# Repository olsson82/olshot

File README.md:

# OlShot
This is an Arduino based Shooting game system. Free to use, you need to make the components your self.

It's wireless and uses nrf24l01 modules to communicate to the targets and the main system.

## How mutch does it cost to buid ?
Well it will cost you some money, for the components, and maufactoring the pcb, **BUT** to have your custom build game is priceless.

## Many Targets
If you are going to use many targets, you need to redesign main unit pcb to work with **ATmega2560** chip (same as in Arduino Mega)
The code here is by default set for 5 targets, but you can adjust it. Test the code in Arduino software when you change to see if your amount of targets
is accepted.

# Read more
* [Wiki](https://github.com/olsson82/olshot/wiki)
* [Targets](page/targets.md)
* [Main Unit](page/mainunit.md)

## Updates
**2023-09-01: Did a redesign on the Nextion Screen. Files uploaded**

**2023-08-31: The clock function is now added to the code, and some adjustments done in the code**

**2023-08-30: The first BETA version of main unit is released.**

**2023-08-04: Working on the code for main unit and design for the touchscreen.**

### Main Unit
**2023-08-01: Kicad files now uploaded**

**2023-07-31: The main unit has been tested and everything seems to be working. The kicad files will soon be uploaded.**

<figure>
    
    <figcaption>Front side of the PCB.</figcaption>
</figure>

### Target PCB
**2023-02-05: The Target PCB Is now avalible for kicad and arduino code.**

Did a redesign of the target sensor, everything is now on the top side. Added jst connections instead of soldering.
<figure>
    
    <figcaption>Front side of the PCB.</figcaption>
</figure>

## Discuss
Feel free to take part in this project. Go to [Discussion](https://github.com/olsson82/olshot/discussions) to ask questions or discuss about the project.

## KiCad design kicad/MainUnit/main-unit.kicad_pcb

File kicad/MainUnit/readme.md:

# Main Unit
This is the main unit. You also need target sensors for it to work.
Please read the WIKI about this main unit before manufactor so you know everything.

Good luck!

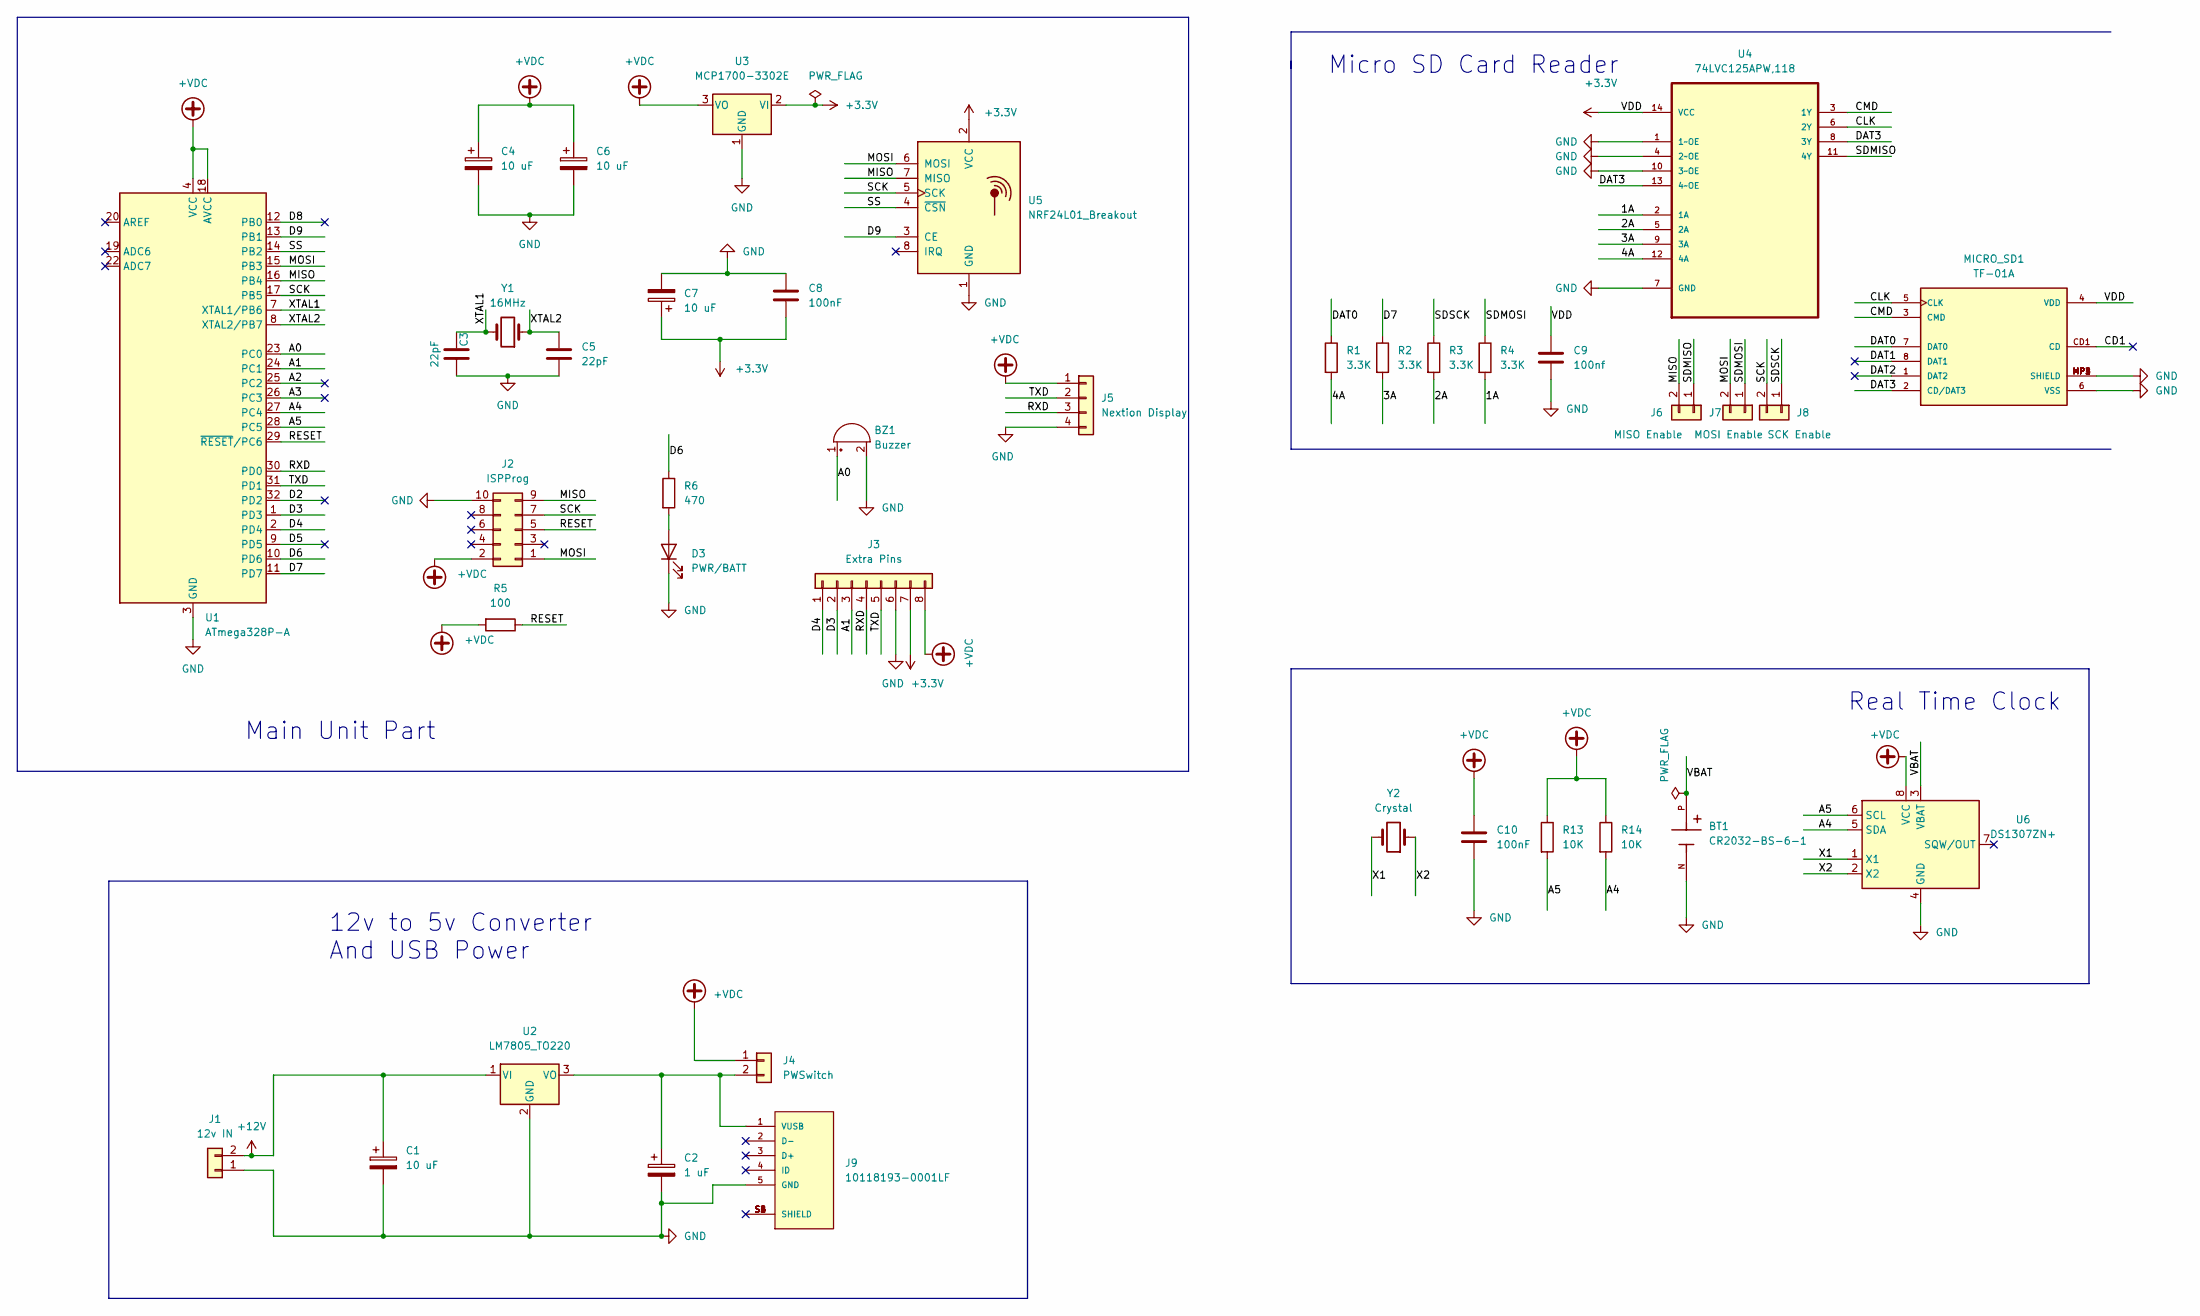
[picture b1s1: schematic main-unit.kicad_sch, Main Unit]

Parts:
BT1: CR2032-BS-6-1; BAT_CR2032-BS-6-1; PARTREV 2011/2/14; LCSC C70377
BZ1: Buzzer; Buzzer_15x7.5RM7.6
C1, C4, C6, C7: 10 uF; CP_Radial_D5.0mm_P2.50mm
C2: 1 uF; CP_Radial_D5.0mm_P2.50mm
C3, C5: 22pF; C_0603_1608Metric; LCSC C1653
C8, C10: 100nF; C_Disc_D5.0mm_W2.5mm_P2.50mm
C9: 100nf; C_Disc_D5.0mm_W2.5mm_P2.50mm
D3: PWR/BATT; LED_D5.0mm
J1: 12v IN; JST_EH_B2B-EH-A_1x02_P2.50mm_Vertical
J2: ISPProg; IDC-Header_2x05_P2.54mm_Vertical
J3: Extra Pins; PinHeader_1x08_P2.54mm_Vertical
J4: PWSwitch; JST_EH_B2B-EH-A_1x02_P2.50mm_Vertical
J5: Nextion Display; JST_EH_B4B-EH-A_1x04_P2.50mm_Vertical
J6: MISO Enable; PinHeader_1x02_P2.54mm_Vertical
J7: MOSI Enable; PinHeader_1x02_P2.54mm_Vertical
J8: SCK Enable; PinHeader_1x02_P2.54mm_Vertical
J9: 10118193-0001LF; FCI_10118193-0001LF; LCSC C381144
MICRO_SD1: TF-01A; LCSC C91145
R1, R2, R3, R4: 3.3K; R_0603_1608Metric; LCSC C22978
R5: 100; R_0603_1608Metric; LCSC C22775
R6: 470; R_0603_1608Metric; LCSC C23179
R13, R14: 10K; R_0603_1608Metric; LCSC C25804
U1: ATmega328P-A; TQFP-32_7x7mm_P0.8mm; LCSC C14877
U2: LM7805_TO220; TO-220-3_Vertical
U3: MCP1700-3302E; TO-92_Inline
U4: 74LVC125APW,118; SOP65P640X110-14N; MPN 74LVC125APW,118; LCSC C6059
U5: NRF24L01_Breakout; nRF24L01_Breakout
U6: DS1307ZN+; SOIC-8_3.9x4.9mm_P1.27mm; LCSC C356706
Y1: 16MHz; Crystal_HC18-U_Vertical
Y2: Crystal; Crystal_AT310_D3.0mm_L10.0mm_Horizontal

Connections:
+3.3V: C7.1, C8.2, C9.1, J3.7, MICRO_SD1.4 (VDD), U3.2 (VI), U4.14 (VCC), U5.2 (VCC)
+12V: C1.1, J1.2, U2.1 (VI)
+VDC: C4.1, C6.1, C10.2, J2.2, J3.8, J4.1, J5.1, R5.2, R13.1, R14.1, U1.4 (VCC), U1.6 (VCC), U1.18 (AVCC), U3.3 (VO), U6.8 (VCC)
/1A: R4.2, U4.2 (1A)
/2A: R3.2, U4.5 (2A)
/3A: R2.2, U4.9 (3A)
/4A: R1.2, U4.12 (4A)
/A0: BZ1.1 (-), U1.23 (PC0)
/A1: J3.3, U1.24 (PC1)
/A2: U1.25 (PC2)
/A3: U1.26 (PC3)
/A4: R14.2, U1.27 (PC4), U6.5 (SDA)
/A5: R13.2, U1.28 (PC5), U6.6 (SCL)
/CD1: MICRO_SD1.CD1 (CD)
/CLK: MICRO_SD1.5 (CLK), U4.6 (2Y)
/CMD: MICRO_SD1.3 (CMD), U4.3 (1Y)
/D2: U1.32 (PD2)
/D3: J3.2, U1.1 (PD3)
/D4: J3.1, U1.2 (PD4)
/D5: U1.9 (PD5)
/D6: R6.1, U1.10 (PD6)
/D7: R2.1, U1.11 (PD7)
/D8: U1.12 (PB0)
/D9: U1.13 (PB1), U5.3 (CE)
/DAT0: MICRO_SD1.7 (DAT0), R1.1
/DAT1: MICRO_SD1.8 (DAT1)
/DAT2: MICRO_SD1.1 (DAT2)
/DAT3: MICRO_SD1.2 (CD/DAT3), U4.8 (3Y), U4.13 (4~OE)
/MISO: J2.9, J6.2, U1.16 (PB4), U5.7 (MISO)
/MOSI: J2.1, J7.2, U1.15 (PB3), U5.6 (MOSI)
/RESET: J2.5, R5.1, U1.29 (~RESET/PC6)
/RXD: J3.4, J5.3, U1.30 (PD0)
/SCK: J2.7, J8.2, U1.17 (PB5), U5.5 (SCK)
/SDMISO: J6.1, U4.11 (4Y)
/SDMOSI: J7.1, R4.1
/SDSCK: J8.1, R3.1
/SS: U1.14 (PB2), U5.4 (~CSN)
/TXD: J3.5, J5.2, U1.31 (PD1)
/VBAT: BT1.P, U6.3 (VBAT)
/X1: U6.1 (X1), Y2.2
/X2: U6.2 (X2), Y2.1
/XTAL1: C3.1, U1.7 (XTAL1/PB6), Y1.2
/XTAL2: C5.2, U1.8 (XTAL2/PB7), Y1.1
GND: BT1.N, BZ1.2 (+), C1.2, C2.2, C3.2, C4.2, C5.1, C6.2, C7.2, C8.1, C9.2, C10.1, D3.1 (K), J1.1, J2.10, J3.6, J5.4, J9.5 (GND), MICRO_SD1.6 (VSS), MICRO_SD1.MP1 (SHIELD), MICRO_SD1.MP2 (SHIELD), MICRO_SD1.MP3 (SHIELD), MICRO_SD1.MP4 (SHIELD), U1.3 (GND), U1.5 (GND), U1.21 (GND), U2.2 (GND), U3.1 (GND), U4.1 (1~OE), U4.4 (2~OE), U4.7 (GND), U4.10 (3~OE), U5.1 (GND), U6.4 (GND)
unnamed: C2.1, J4.2, J9.1 (VUSB), U2.3 (VO)
unnamed: D3.2 (A), R6.2

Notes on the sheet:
Micro SD Card Reader
Main Unit Part
12v to 5v Converter And USB Power
Real Time Clock

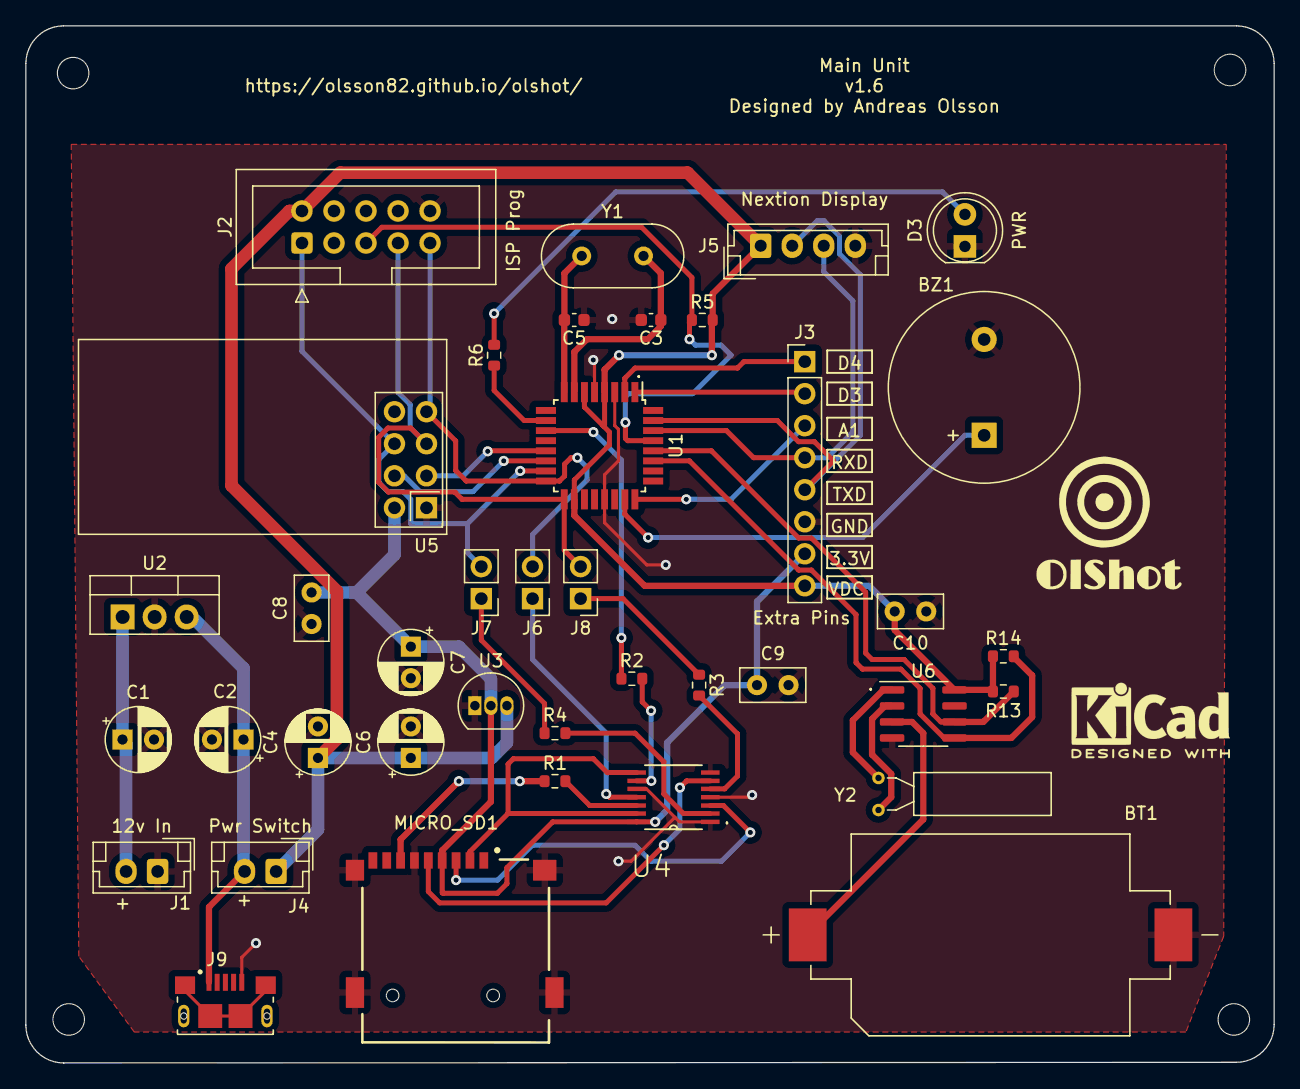
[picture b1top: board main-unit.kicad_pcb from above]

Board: 2 copper layers, 99.0 x 82.2 mm, 39 parts (0 on the bottom side), 38 nets.

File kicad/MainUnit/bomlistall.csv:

Component Count:,39,,,,
Ref,Qnty,Value,Cmp name,Footprint,Description
"BT1, ",1,CR2032-BS-6-1,CR2032-BS-6-1,BAT_CR2032-BS-6-1,
"BZ1, ",1,Buzzer,Buzzer,Buzzer_Beeper:Buzzer_15x7.5RM7.6,"Buzzer, polarized"
"C1, C4, C6, C7, ",4,10 uF,C_Polarized,Capacitor_THT:CP_Radial_D5.0mm_P2.50mm,Polarized capacitor
"C2, ",1,1 uF,C_Polarized,Capacitor_THT:CP_Radial_D5.0mm_P2.50mm,Polarized capacitor
"C3, C5, ",2,22pF,C,Capacitor_SMD:C_0603_1608Metric,Unpolarized capacitor
"C8, C10, ",2,100nF,C,Capacitor_THT:C_Disc_D5.0mm_W2.5mm_P2.50mm,Unpolarized capacitor
"C9, ",1,100nf,C,Capacitor_THT:C_Disc_D5.0mm_W2.5mm_P2.50mm,Unpolarized capacitor
"D3, ",1,PWR/BATT,LED,LED_THT:LED_D5.0mm,Light emitting diode
"J1, ",1,12v IN,Conn_01x02,Connector_JST:JST_EH_B2B-EH-A_1x02_P2.50mm_Vertical,"Generic connector, single row, 01x02, script generated (kicad-library-utils/schlib/autogen/connector/)"
"J2, ",1,ISPProg,Conn_02x05_Odd_Even,Connector_IDC:IDC-Header_2x05_P2.54mm_Vertical,"Generic connector, double row, 02x05, odd/even pin numbering scheme (row 1 odd numbers, row 2 even numbers), script generated (kicad-library-utils/schlib/autogen/connector/)"
"J3, ",1,Extra Pins,Conn_01x08,Connector_PinHeader_2.54mm:PinHeader_1x08_P2.54mm_Vertical,"Generic connector, single row, 01x08, script generated (kicad-library-utils/schlib/autogen/connector/)"
"J4, ",1,PWSwitch,Conn_01x02,Connector_JST:JST_EH_B2B-EH-A_1x02_P2.50mm_Vertical,"Generic connector, single row, 01x02, script generated (kicad-library-utils/schlib/autogen/connector/)"
"J5, ",1,Nextion Display,Conn_01x04,Connector_JST:JST_EH_B4B-EH-A_1x04_P2.50mm_Vertical,"Generic connector, single row, 01x04, script generated (kicad-library-utils/schlib/autogen/connector/)"
"J6, ",1,MISO Enable,Conn_01x02,Connector_PinHeader_2.54mm:PinHeader_1x02_P2.54mm_Vertical,"Generic connector, single row, 01x02, script generated (kicad-library-utils/schlib/autogen/connector/)"
"J7, ",1,MOSI Enable,Conn_01x02,Connector_PinHeader_2.54mm:PinHeader_1x02_P2.54mm_Vertical,"Generic connector, single row, 01x02, script generated (kicad-library-utils/schlib/autogen/connector/)"
"J8, ",1,SCK Enable,Conn_01x02,Connector_PinHeader_2.54mm:PinHeader_1x02_P2.54mm_Vertical,"Generic connector, single row, 01x02, script generated (kicad-library-utils/schlib/autogen/connector/)"
"J9, ",1,10118193-0001LF,10118193-0001LF,10118193-0001LF:FCI_10118193-0001LF,
"MICRO_SD1, ",1,TF-01A,TF-01A,TF-01A,
"R1, R2, R3, R4, ",4,3.3K,R,Resistor_SMD:R_0603_1608Metric,Resistor
"R5, ",1,100,R,Resistor_SMD:R_0603_1608Metric,Resistor
"R6, ",1,470,R,Resistor_SMD:R_0603_1608Metric,Resistor
"R13, R14, ",2,10K,R,Resistor_SMD:R_0603_1608Metric,Resistor
"U1, ",1,ATmega328P-A,ATmega328P-A,Package_QFP:TQFP-32_7x7mm_P0.8mm,"20MHz, 32kB Flash, 2kB SRAM, 1kB EEPROM, TQFP-32"
"U2, ",1,LM7805_TO220,LM7805_TO220,Package_TO_SOT_THT:TO-220-3_Vertical,"Positive 1A 35V Linear Regulator, Fixed Output 5V, TO-220"
"U3, ",1,MCP1700-3302E,MCP1700x-330xxTO,Package_TO_SOT_THT:TO-92_Inline,"250mA Low Quiscent Current LDO, 3.3V output, TO-92"
"U4, ",1,"74LVC125APW,118","74LVC125APW,118",74LVC125APW_118:SOP65P640X110-14N,
"U5, ",1,NRF24L01_Breakout,NRF24L01_Breakout,RF_Module:nRF24L01_Breakout,"Ultra low power 2.4GHz RF Transceiver, Carrier PCB"
"U6, ",1,DS1307ZN+,DS1307ZN+,Package_SO:SOIC-8_3.9x4.9mm_P1.27mm,"64 x 8, Serial, I2C Real-time clock, 4.5V to 5.5V VCC, -40°C to +85°C, SOIC-8"
"Y1, ",1,16MHz,Crystal,Crystal:Crystal_HC18-U_Vertical,Two pin crystal
"Y2, ",1,Crystal,Crystal,Crystal:Crystal_AT310_D3.0mm_L10.0mm_Horizontal,Two pin crystal

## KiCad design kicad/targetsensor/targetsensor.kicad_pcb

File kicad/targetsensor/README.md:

# Target Sensor
This is the target sensor. You also need the main unit for it to work.
Please read the WIKI about this sensors before manufactor so you know everything.

Good luck!

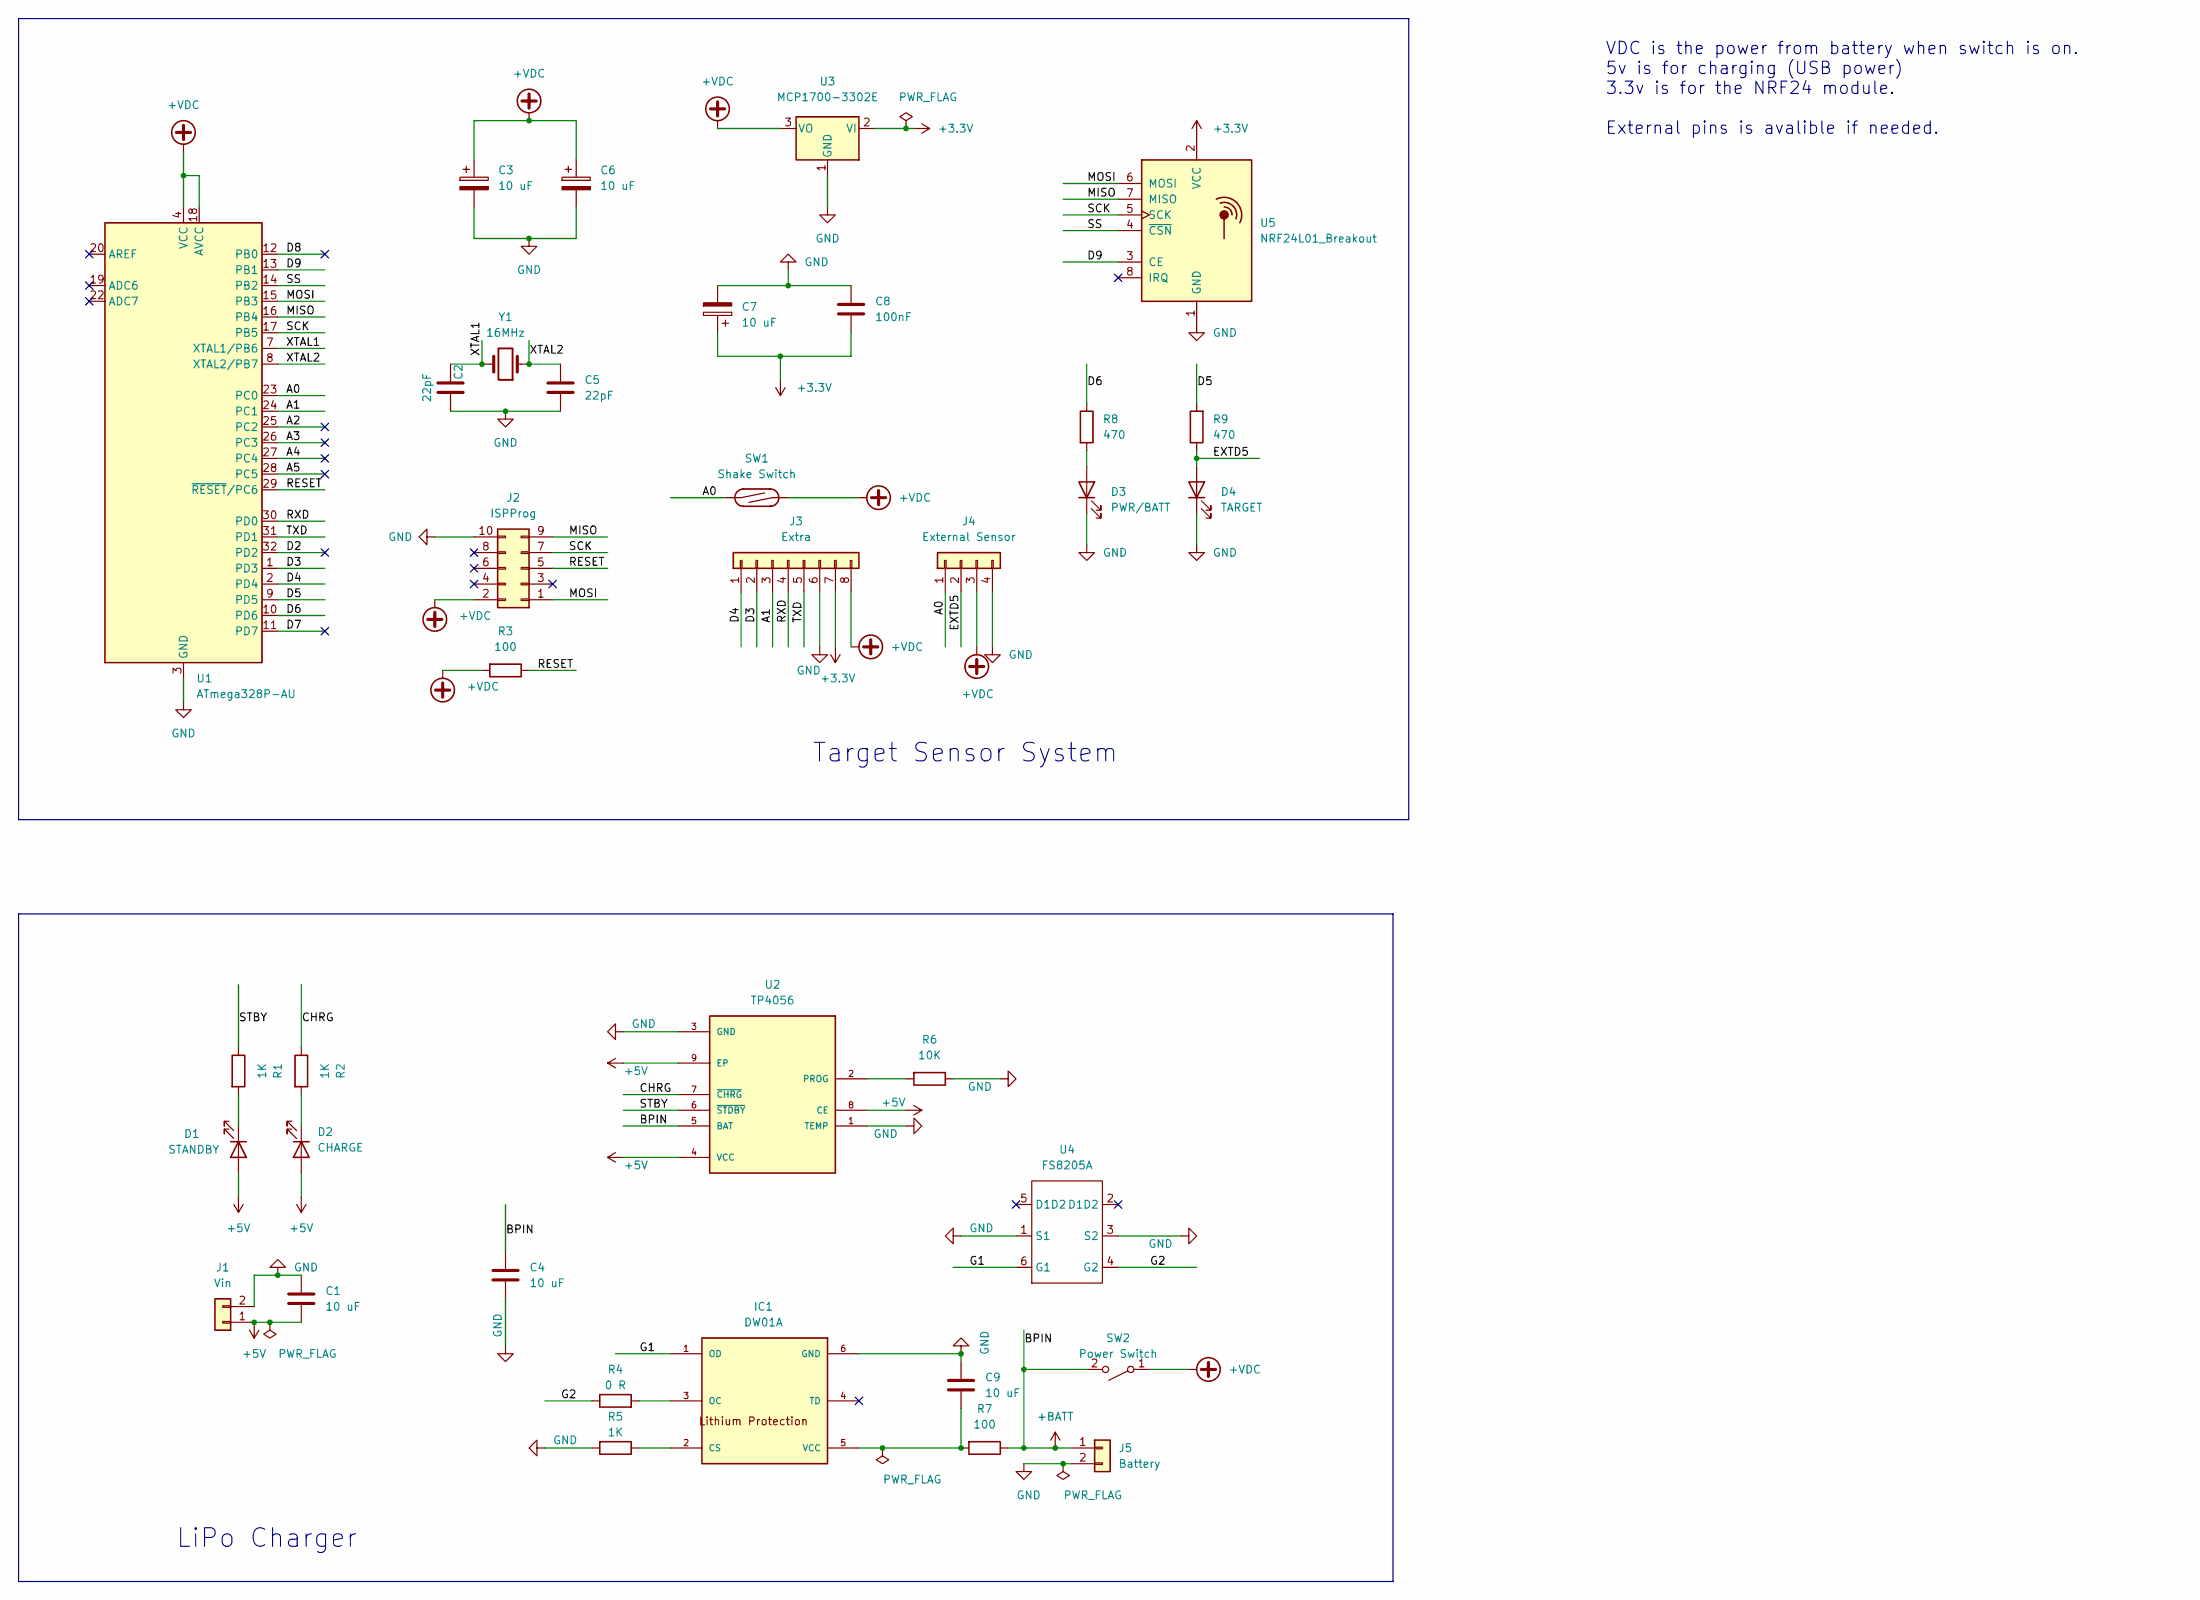
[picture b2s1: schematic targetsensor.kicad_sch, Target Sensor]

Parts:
C1, C4, C9: 10 uF; C_0603_1608Metric; LCSC C96446
C2, C5: 22pF; C_0603_1608Metric; LCSC C1653
C3, C6, C7: 10 uF; CP_Radial_D5.0mm_P2.50mm
C8: 100nF; C_Disc_D5.0mm_W2.5mm_P2.50mm
D1: STANDBY; LED_D5.0mm
D2: CHARGE; LED_D5.0mm
D3: PWR/BATT; LED_D5.0mm
D4: TARGET; LED_D5.0mm
IC1: DW01A; SOT23-6; MPN DW01A; LCSC C181096
J1: Vin; JST_EH_B2B-EH-A_1x02_P2.50mm_Vertical
J2: ISPProg; IDC-Header_2x05_P2.54mm_Vertical
J3: Extra; PinHeader_1x08_P2.54mm_Vertical
J4: External Sensor; JST_EH_B4B-EH-A_1x04_P2.50mm_Vertical
J5: Battery; JST_EH_B2B-EH-A_1x02_P2.50mm_Vertical
R1, R2, R5: 1K; R_0603_1608Metric; LCSC C21190
R3, R7: 100; R_0603_1608Metric; LCSC C22775
R4: 0 R; R_0603_1608Metric; LCSC C21189
R6: 10K; R_0603_1608Metric; LCSC C25804
R8, R9: 470; R_0603_1608Metric; LCSC C23179
SW1: Shake Switch; JST_EH_B2B-EH-A_1x02_P2.50mm_Vertical
SW2: Power Switch; JST_EH_B2B-EH-A_1x02_P2.50mm_Vertical
U1: ATmega328P-AU; TQFP-32_7x7mm_P0.8mm; LCSC C14877
U2: TP4056; SOP127P600X175-9N; LCSC C16581
U3: MCP1700-3302E; TO-92_Inline
U4: FS8205A; SOT-23-6; LCSC C2830320
U5: NRF24L01_Breakout; nRF24L01_Breakout
Y1: 16MHz; Crystal_HC18-U_Vertical

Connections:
+3.3V: C7.1, C8.2, J3.7, U3.2 (VI), U5.2 (VCC)
+5V: C1.2, D1.2 (A), D2.2 (A), J1.1, U2.4 (VCC), U2.8 (CE), U2.9 (EP)
+BATT: C4.1, J5.1, R7.1, SW2.2 (B), U2.5 (BAT)
+VDC: C3.1, C6.1, J2.2, J3.8, J4.3, R3.2, SW1.2, SW2.1 (A), U1.4 (VCC), U1.6 (VCC), U1.18 (AVCC), U3.3 (VO)
/A0: J4.1, SW1.1, U1.23 (PC0)
/A1: J3.3, U1.24 (PC1)
/A2: U1.25 (PC2)
/A3: U1.26 (PC3)
/A4: U1.27 (PC4)
/A5: U1.28 (PC5)
/CHRG: R2.1, U2.7 (~CHRG)
/D2: U1.32 (PD2)
/D3: J3.2, U1.1 (PD3)
/D4: J3.1, U1.2 (PD4)
/D5: R9.2, U1.9 (PD5)
/D6: R8.1, U1.10 (PD6)
/D7: U1.11 (PD7)
/D8: U1.12 (PB0)
/D9: U1.13 (PB1), U5.3 (CE)
/EXTD5: D4.2 (A), J4.2, R9.1
/G1: IC1.1 (OD), U4.6 (G1)
/G2: R4.1, U4.4 (G2)
/MISO: J2.9, U1.16 (PB4), U5.7 (MISO)
/MOSI: J2.1, U1.15 (PB3), U5.6 (MOSI)
/RESET: J2.5, R3.1, U1.29 (~RESET/PC6)
/RXD: J3.4, U1.30 (PD0)
/SCK: J2.7, U1.17 (PB5), U5.5 (SCK)
/SS: U1.14 (PB2), U5.4 (~CSN)
/STBY: R1.1, U2.6 (~STDBY)
/TXD: J3.5, U1.31 (PD1)
/XTAL1: C2.1, U1.7 (XTAL1/PB6), Y1.2
/XTAL2: C5.2, U1.8 (XTAL2/PB7), Y1.1
GND: C1.1, C2.2, C3.2, C4.2, C5.1, C6.2, C7.2, C8.1, C9.1, D3.1 (K), D4.1 (K), IC1.6 (GND), J1.2, J2.10, J3.6, J4.4, J5.2, R5.2, R6.1, U1.3 (GND), U1.5 (GND), U1.21 (GND), U2.1 (TEMP), U2.3 (GND), U3.1 (GND), U4.1 (S1), U4.3 (S2), U5.1 (GND)
unnamed: C9.2, IC1.5 (VCC), R7.2
unnamed: D1.1 (K), R1.2
unnamed: D2.1 (K), R2.2
unnamed: D3.2 (A), R8.2
unnamed: IC1.2 (CS), R5.1
unnamed: IC1.3 (OC), R4.2
unnamed: R6.2, U2.2 (PROG)

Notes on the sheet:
VDC is the power from battery when switch is on. 5v is for charging (USB power) 3.3v is for the NRF24 module. External pins is avalible if needed.
LiPo Charger
Target Sensor System

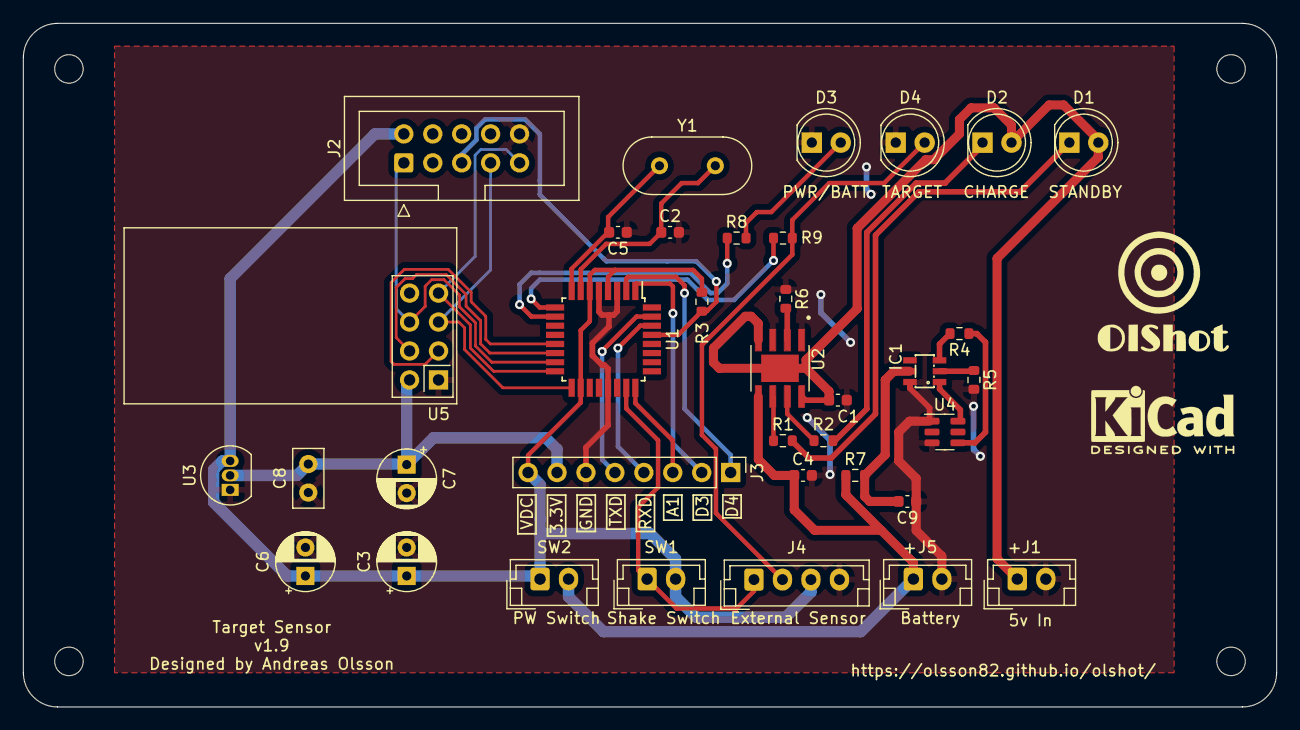
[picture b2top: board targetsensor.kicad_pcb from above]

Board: 2 copper layers, 110.0 x 60.0 mm, 36 parts (0 on the bottom side), 33 nets.

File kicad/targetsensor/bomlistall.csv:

Component Count:,36,,,,,
Ref,Qnty,Value,Cmp name,Footprint,Description,Vendor
"C1, C4, C9, ",3,10 uF,C,Capacitor_SMD:C_0603_1608Metric,Unpolarized capacitor,
"C2, C5, ",2,22pF,C,Capacitor_SMD:C_0603_1608Metric,Unpolarized capacitor,
"C3, C6, C7, ",3,10 uF,C_Polarized,Capacitor_THT:CP_Radial_D5.0mm_P2.50mm,Polarized capacitor,
"C8, ",1,100nF,C,Capacitor_THT:C_Disc_D5.0mm_W2.5mm_P2.50mm,Unpolarized capacitor,
"D1, ",1,STANDBY,LED,LED_THT:LED_D5.0mm,Light emitting diode,
"D2, ",1,CHARGE,LED,LED_THT:LED_D5.0mm,Light emitting diode,
"D3, ",1,PWR/BATT,LED,LED_THT:LED_D5.0mm,Light emitting diode,
"D4, ",1,TARGET,LED,LED_THT:LED_D5.0mm,Light emitting diode,
"IC1, ",1,DW01A,DW01A,SOT23-6,,
"J1, ",1,Vin,Conn_01x02,Connector_JST:JST_EH_B2B-EH-A_1x02_P2.50mm_Vertical,"Generic connector, single row, 01x02, script generated (kicad-library-utils/schlib/autogen/connector/)",
"J2, ",1,ISPProg,Conn_02x05_Odd_Even,Connector_IDC:IDC-Header_2x05_P2.54mm_Vertical,"Generic connector, double row, 02x05, odd/even pin numbering scheme (row 1 odd numbers, row 2 even numbers), script generated (kicad-library-utils/schlib/autogen/connector/)",
"J3, ",1,Extra,Conn_01x08,Connector_PinHeader_2.54mm:PinHeader_1x08_P2.54mm_Vertical,"Generic connector, single row, 01x08, script generated (kicad-library-utils/schlib/autogen/connector/)",
"J4, ",1,External Sensor,Conn_01x04,Connector_JST:JST_EH_B4B-EH-A_1x04_P2.50mm_Vertical,"Generic connector, single row, 01x04, script generated (kicad-library-utils/schlib/autogen/connector/)",
"J5, ",1,Battery,Conn_01x02,Connector_JST:JST_EH_B2B-EH-A_1x02_P2.50mm_Vertical,"Generic connector, single row, 01x02, script generated (kicad-library-utils/schlib/autogen/connector/)",
"R1, R2, R5, ",3,1K,R,Resistor_SMD:R_0603_1608Metric,Resistor,
"R3, R7, ",2,100,R,Resistor_SMD:R_0603_1608Metric,Resistor,
"R4, ",1,0 R,R,Resistor_SMD:R_0603_1608Metric,Resistor,
"R6, ",1,10K,R,Resistor_SMD:R_0603_1608Metric,Resistor,
"R8, R9, ",2,470,R,Resistor_SMD:R_0603_1608Metric,Resistor,
"SW1, ",1,Shake Switch,SW_Reed,Connector_JST:JST_EH_B2B-EH-A_1x02_P2.50mm_Vertical,reed switch,
"SW2, ",1,Power Switch,SW_SPST,Connector_JST:JST_EH_B2B-EH-A_1x02_P2.50mm_Vertical,Single Pole Single Throw (SPST) switch,
"U1, ",1,ATmega328P-AU,ATmega328P-A,Package_QFP:TQFP-32_7x7mm_P0.8mm,"20MHz, 32kB Flash, 2kB SRAM, 1kB EEPROM, TQFP-32",
"U2, ",1,TP4056,TP4056,SOP127P600X175-9N,,
"U3, ",1,MCP1700-3302E,MCP1700x-330xxTO,Package_TO_SOT_THT:TO-92_Inline,"250mA Low Quiscent Current LDO, 3.3V output, TO-92",
"U4, ",1,FS8205A,FS8205A,Package_TO_SOT_SMD:SOT-23-6,FS8205A,
"U5, ",1,NRF24L01_Breakout,NRF24L01_Breakout,RF_Module:nRF24L01_Breakout,"Ultra low power 2.4GHz RF Transceiver, Carrier PCB",
"Y1, ",1,16MHz,Crystal,Crystal:Crystal_HC18-U_Vertical,Two pin crystal,

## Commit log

2023-01-14 Spell Corrections
2023-01-14 Created main.cpp
    The code is not done, still under development.
2023-01-15 Added image of PCB for target
    The first layout of pcb for target sensor board.
2023-01-15 Customize targets.md
2023-01-17 Added Schematic for main unit
2023-01-21 New version of target sensor
2023-01-22 Create mainunit
2023-02-05 Added the program to target sensor
2023-08-06 Failsafe time comes from main unit now
2023-08-30 Added files for the display
2023-08-30 Added the main unit code
2023-08-31 Updated with support for set time
2023-08-31 Now with clock function
2023-09-01 Better design now
2023-09-01 Fixed correct title for rapidfire
2023-09-06 Added Y2 Crystal kHz
